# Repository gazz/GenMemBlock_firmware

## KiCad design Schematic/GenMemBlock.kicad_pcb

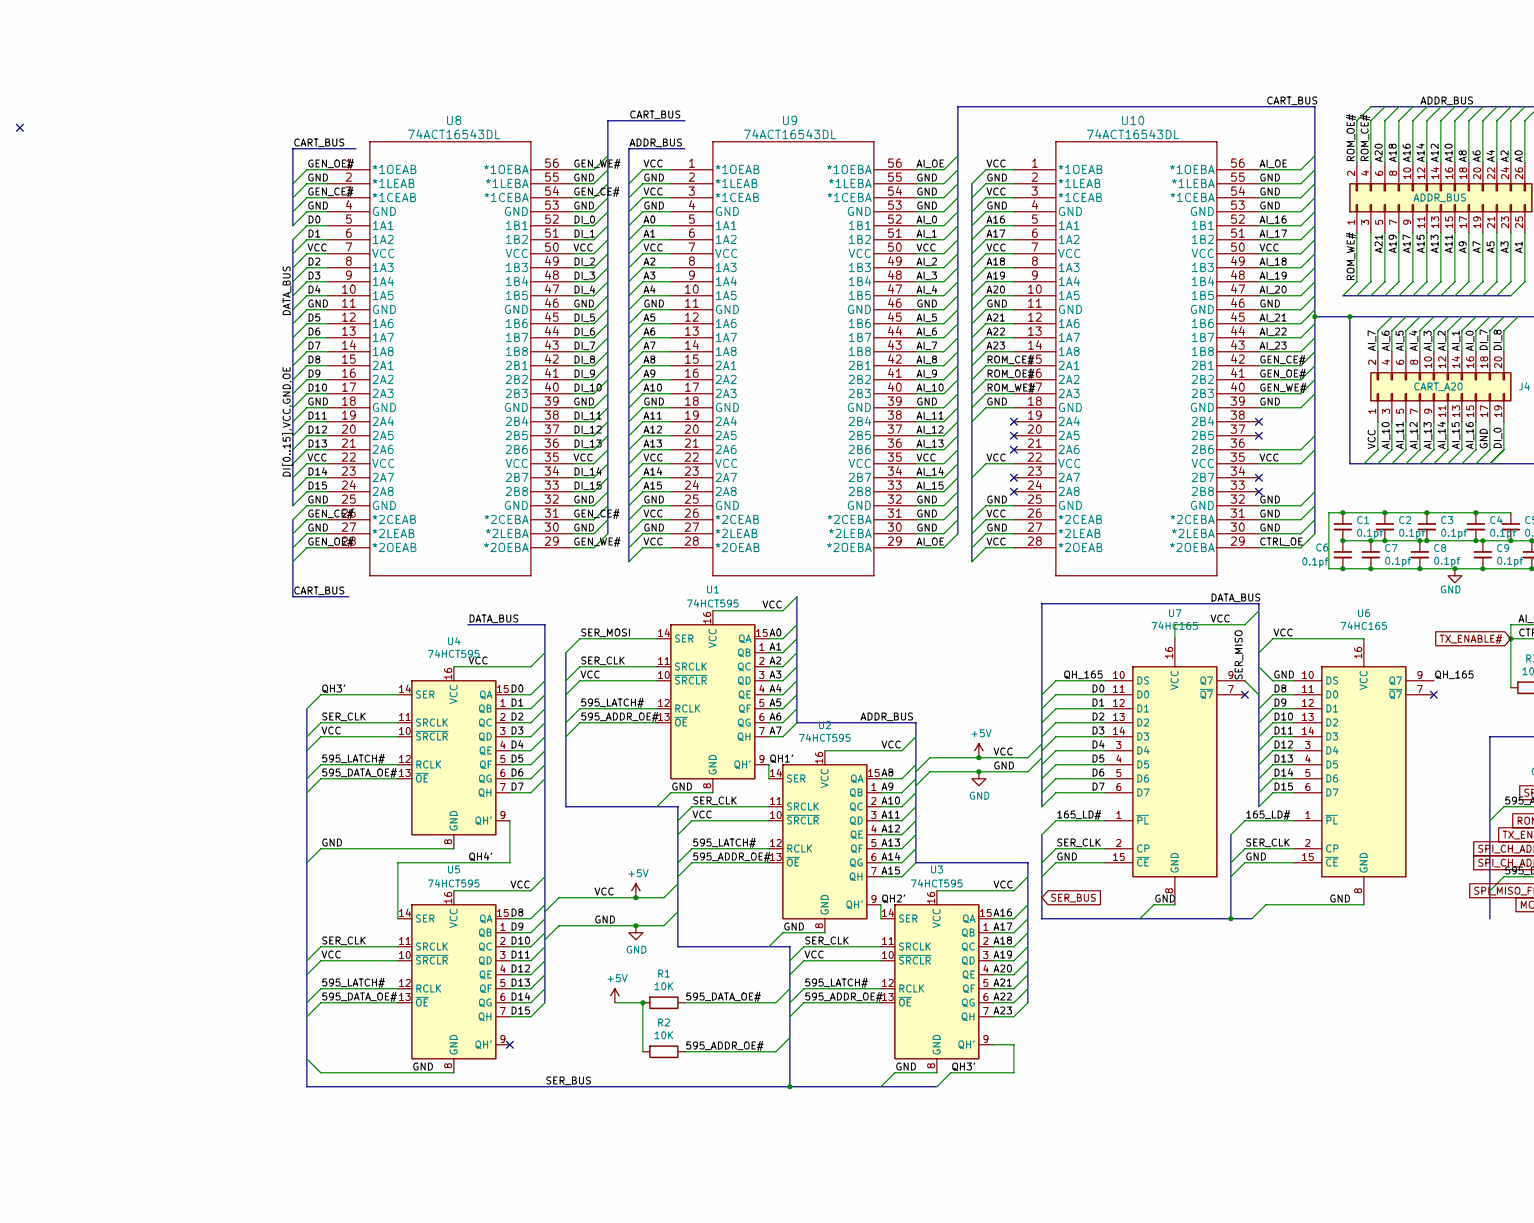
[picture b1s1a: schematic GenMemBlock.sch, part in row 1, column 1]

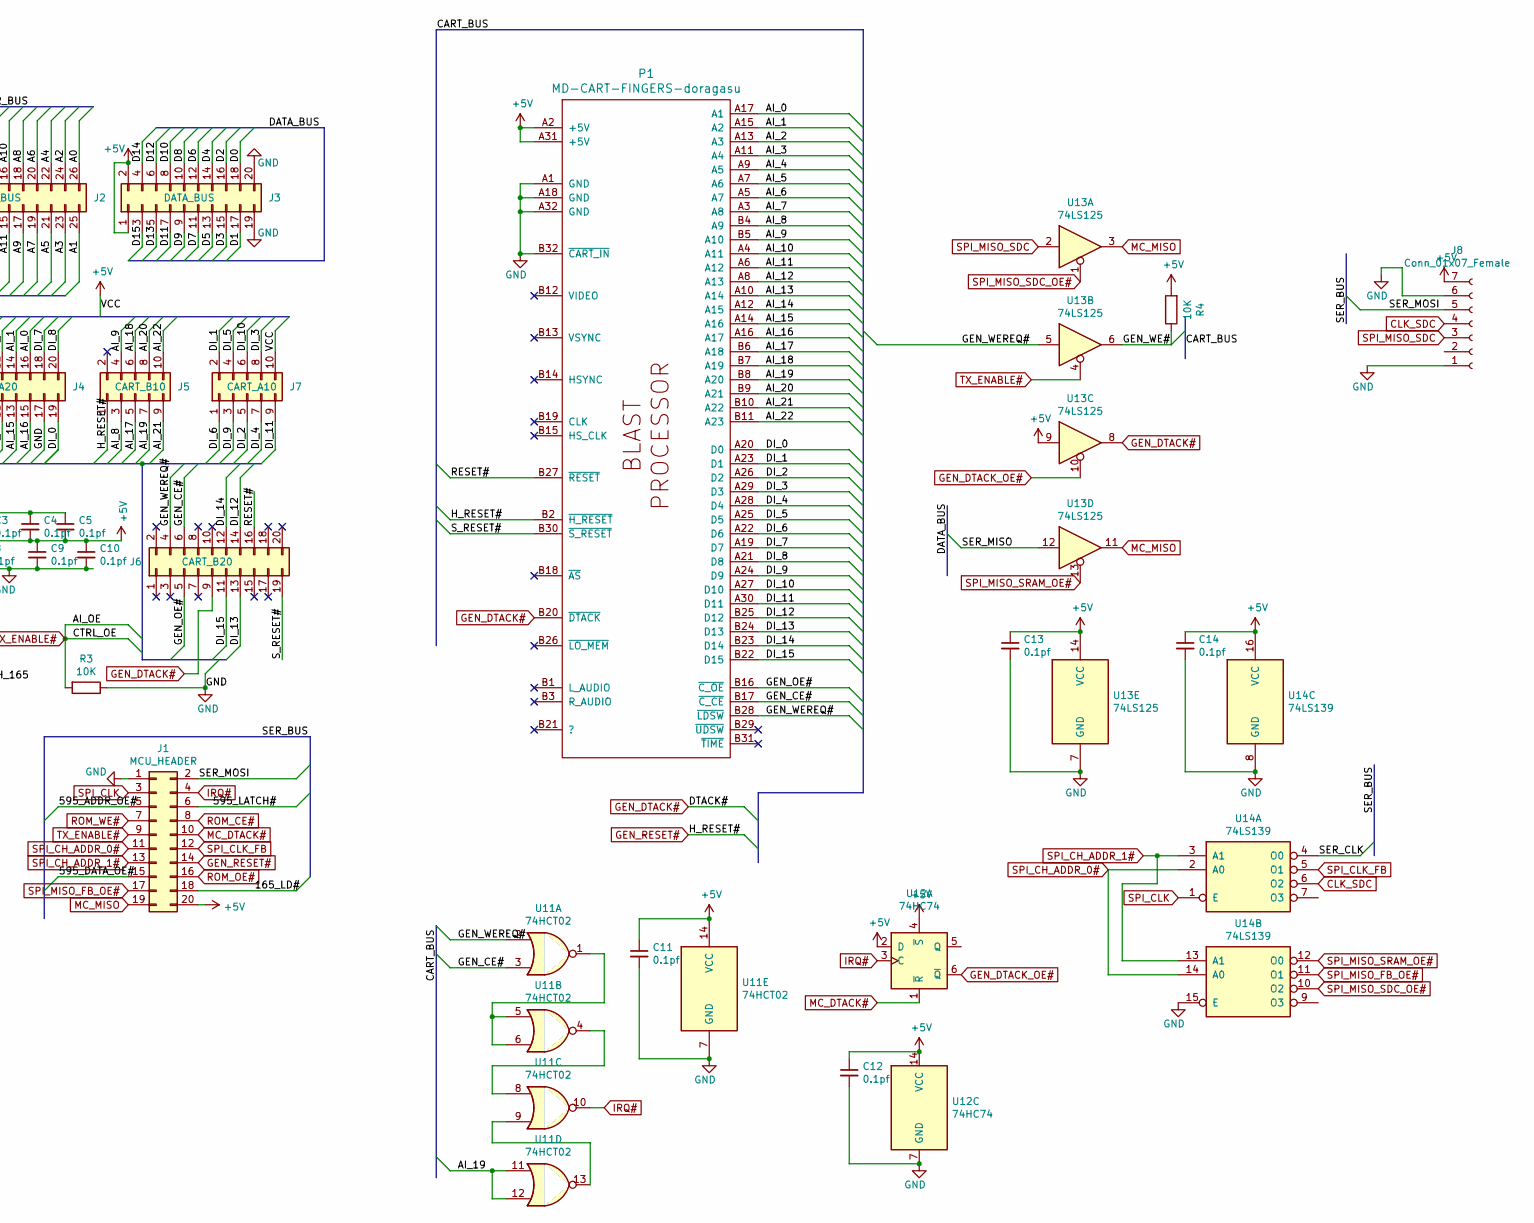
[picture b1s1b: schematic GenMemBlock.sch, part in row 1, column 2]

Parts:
C1, C2, C3, C4, C5, C6, C7, C8, C9, C10, C11, C12, C13, C14: 0.1pf; C_0805_2012Metric_Pad1.18x1.45mm_HandSolder
J1: MCU_HEADER; PinHeader_2x10_P2.54mm_Vertical
J2: ADDR_BUS; PinHeader_2x13_P2.54mm_Vertical
J3: DATA_BUS; PinHeader_2x10_P2.54mm_Vertical
J4: CART_A20; PinHeader_2x10_P2.54mm_Vertical
J5: CART_B10; PinHeader_2x05_P2.54mm_Vertical
J6: CART_B20; PinHeader_2x10_P2.54mm_Vertical
J7: CART_A10; PinHeader_2x05_P2.54mm_Vertical
J8: Conn_01x07_Female; PinHeader_1x07_P2.54mm_Vertical
P1: MD-CART-FINGERS-doragasu; md-cart
R1, R2, R3, R4: 10K; R_0805_2012Metric_Pad1.20x1.40mm_HandSolder
U1, U2, U3, U4, U5: 74HCT595; SOIC-16_3.9x9.9mm_P1.27mm
U6, U7: 74HC165; SSOP-16_5.3x6.2mm_P0.65mm
U8, U9, U10: 74ACT16543DL
U11: 74HCT02; TSSOP-14_4.4x5mm_P0.65mm
U12: 74HC74; TSSOP-14_4.4x5mm_P0.65mm
U13: 74LS125; TSSOP-14_4.4x5mm_P0.65mm
U14: 74LS139; TSSOP-16_4.4x5mm_P0.65mm

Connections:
+5V: C1.2, C2.2, C3.2, C4.2, C5.2, C6.1, C7.1, C8.1, C9.1, C10.1, C11.1, C12.1, C13.1, C14.1, J1.20, J3.1, J3.2, J4.1, J7.10, J8.7, P1.A2 (+5V), P1.A31 (+5V), R1.2, R2.2, R4.2, U1.10 (~SRCLR), U1.16 (VCC), U2.10 (~SRCLR), U2.16 (VCC), U3.10 (~SRCLR), U3.16 (VCC), U4.10 (~SRCLR), U4.16 (VCC), U5.10 (~SRCLR), U5.16 (VCC), U6.16 (VCC), U7.16 (VCC), U8.7 (VCC), U8.22 (VCC), U8.35 (VCC), U8.50 (VCC), U9.1 (*1OEAB), U9.3 (*1CEAB), U9.7 (VCC), U9.22 (VCC), U9.26 (*2CEAB), U9.28 (*2OEAB), U9.35 (VCC), U9.50 (VCC), U10.1 (*1OEAB), U10.3 (*1CEAB), U10.7 (VCC), U10.22 (VCC), U10.26 (*2CEAB), U10.28 (*2OEAB), U10.35 (VCC), U10.50 (VCC), U11.14 (VCC), U12.2 (D), U12.4 (~S), U12.14 (VCC), U13.9, U13.14 (VCC), U14.16 (VCC)
/165_LD#: J1.18, U6.1 (~PL), U7.1 (~PL)
/595_ADDR_OE#: J1.5, R2.1, U1.13 (~OE), U2.13 (~OE), U3.13 (~OE)
/595_DATA_OE#: J1.15, R1.1, U4.13 (~OE), U5.13 (~OE)
/595_LATCH#: J1.6, U1.12 (RCLK), U2.12 (RCLK), U3.12 (RCLK), U4.12 (RCLK), U5.12 (RCLK)
/A0: J2.26, U1.15 (QA), U9.5 (1A1)
/A1: J2.25, U1.1 (QB), U9.6 (1A2)
/A2: J2.24, U1.2 (QC), U9.8 (1A3)
/A3: J2.23, U1.3 (QD), U9.9 (1A4)
/A4: J2.22, U1.4 (QE), U9.10 (1A5)
/A5: J2.21, U1.5 (QF), U9.12 (1A6)
/A6: J2.20, U1.6 (QG), U9.13 (1A7)
/A7: J2.19, U1.7 (QH), U9.14 (1A8)
/A8: J2.18, U2.15 (QA), U9.15 (2A1)
/A9: J2.17, U2.1 (QB), U9.16 (2A2)
/A10: J2.16, U2.2 (QC), U9.17 (2A3)
/A11: J2.15, U2.3 (QD), U9.19 (2A4)
/A12: J2.14, U2.4 (QE), U9.20 (2A5)
/A13: J2.13, U2.5 (QF), U9.21 (2A6)
/A14: J2.12, U2.6 (QG), U9.23 (2A7)
/A15: J2.11, U2.7 (QH), U9.24 (2A8)
/A16: J2.10, U3.15 (QA), U10.5 (1A1)
/A17: J2.9, U3.1 (QB), U10.6 (1A2)
/A18: J2.8, U3.2 (QC), U10.8 (1A3)
/A19: J2.7, U3.3 (QD), U10.9 (1A4)
/A20: J2.6, U3.4 (QE), U10.10 (1A5)
/A21: J2.5, U3.5 (QF), U10.12 (1A6)
/A22: U3.6 (QG), U10.13 (1A7)
/A23: U3.7 (QH), U10.14 (1A8)
/AI_0: J4.16, P1.A17 (A1), U9.52 (1B1)
/AI_1: J4.14, P1.A15 (A2), U9.51 (1B2)
/AI_2: J4.12, P1.A13 (A3), U9.49 (1B3)
/AI_3: J4.10, P1.A11 (A4), U9.48 (1B4)
/AI_4: J4.8, P1.A9 (A5), U9.47 (1B5)
/AI_5: J4.6, P1.A7 (A6), U9.45 (1B6)
/AI_6: J4.4, P1.A5 (A7), U9.44 (1B7)
/AI_7: J4.2, P1.A3 (A8), U9.43 (1B8)
/AI_8: J5.3, P1.B4 (A9), U9.42 (2B1)
/AI_9: J5.4, P1.B5 (A10), U9.41 (2B2)
/AI_10: J4.3, P1.A4 (A11), U9.40 (2B3)
/AI_11: J4.5, P1.A6 (A12), U9.38 (2B4)
/AI_12: J4.7, P1.A8 (A13), U9.37 (2B5)
/AI_13: J4.9, P1.A10 (A14), U9.36 (2B6)
/AI_14: J4.11, P1.A12 (A15), U9.34 (2B7)
/AI_15: J4.13, P1.A14 (A16), U9.33 (2B8)
/AI_16: J4.15, P1.A16 (A17), U10.52 (1B1)
/AI_17: J5.5, P1.B6 (A18), U10.51 (1B2)
/AI_18: J5.6, P1.B7 (A19), U10.49 (1B3)
/AI_19: J5.7, P1.B8 (A20), U10.48 (1B4), U11.11, U11.12
/AI_20: J5.8, P1.B9 (A21), U10.47 (1B5)
/AI_21: J5.9, P1.B10 (A22), U10.45 (1B6)
/AI_22: J5.10, P1.B11 (A23), U10.44 (1B7)
/AI_23: U10.43 (1B8)
/D0: J3.18, U4.15 (QA), U7.11 (D0), U8.5 (1A1)
/D1: J3.17, U4.1 (QB), U7.12 (D1), U8.6 (1A2)
/D2: J3.16, U4.2 (QC), U7.13 (D2), U8.8 (1A3)
/D3: J3.15, U4.3 (QD), U7.14 (D3), U8.9 (1A4)
/D4: J3.14, U4.4 (QE), U7.3 (D4), U8.10 (1A5)
/D5: J3.13, U4.5 (QF), U7.4 (D5), U8.12 (1A6)
/D6: J3.12, U4.6 (QG), U7.5 (D6), U8.13 (1A7)
/D7: J3.11, U4.7 (QH), U7.6 (D7), U8.14 (1A8)
/D8: J3.10, U5.15 (QA), U6.11 (D0), U8.15 (2A1)
/D9: J3.9, U5.1 (QB), U6.12 (D1), U8.16 (2A2)
/D10: J3.8, U5.2 (QC), U6.13 (D2), U8.17 (2A3)
/D11: J3.7, U5.3 (QD), U6.14 (D3), U8.19 (2A4)
/D12: J3.6, U5.4 (QE), U6.3 (D4), U8.20 (2A5)
/D13: J3.5, U5.5 (QF), U6.4 (D5), U8.21 (2A6)
/D14: J3.4, U5.6 (QG), U6.5 (D6), U8.23 (2A7)
/D15: J3.3, U5.7 (QH), U6.6 (D7), U8.24 (2A8)
/DI_0: J4.19, P1.A20 (D0), U8.52 (1B1)
/DI_1: J7.2, P1.A23 (D1), U8.51 (1B2)
/DI_2: J7.5, P1.A26 (D2), U8.49 (1B3)
/DI_3: J7.8, P1.A29 (D3), U8.48 (1B4)
/DI_4: J7.7, P1.A28 (D4), U8.47 (1B5)
/DI_5: J7.4, P1.A25 (D5), U8.45 (1B6)
/DI_6: J7.1, P1.A22 (D6), U8.44 (1B7)
/DI_7: J4.18, P1.A19 (D7), U8.43 (1B8)
/DI_8: J4.20, P1.A21 (D8), U8.42 (2B1)
/DI_9: J7.3, P1.A24 (D9), U8.41 (2B2)
/DI_10: J7.6, P1.A27 (D10), U8.40 (2B3)
/DI_11: J7.9, P1.A30 (D11), U8.38 (2B4)
/DI_12: J6.14, P1.B25 (D12), U8.37 (2B5)
/DI_13: J6.13, P1.B24 (D13), U8.36 (2B6)
/DI_14: J6.12, P1.B23 (D14), U8.34 (2B7)
/DI_15: J6.11, P1.B22 (D15), U8.33 (2B8)
/GEN_CE#: J6.6, P1.B17 (~C_CE), U8.3 (*1CEAB), U8.26 (*2CEAB), U8.31 (*2CEBA), U8.54 (*1CEBA), U10.42 (2B1), U11.3
/GEN_OE#: J6.5, P1.B16 (~C_OE), U8.1 (*1OEAB), U8.28 (*2OEAB), U10.41 (2B2)
/GEN_WE#: R4.1, U8.29 (*2OEBA), U8.56 (*1OEBA), U10.40 (2B3), U13.6
/GEN_WEREQ#: J6.4, P1.B28 (~LDSW), U11.2, U13.5
/QH1': U1.9 (QH'), U2.14 (SER)
/QH2': U2.9 (QH'), U3.14 (SER)
/QH3': U3.9 (QH'), U4.14 (SER)
/QH4': U4.9 (QH'), U5.14 (SER)
/QH_165: U6.9 (Q7), U7.10 (DS)
/RESET#: J6.16, P1.B27 (~RESET)
/SER_CLK: U1.11 (SRCLK), U2.11 (SRCLK), U3.11 (SRCLK), U4.11 (SRCLK), U5.11 (SRCLK), U6.2 (CP), U7.2 (CP), U14.4 (O0)
/SER_MISO: U7.9 (Q7), U13.12
/SER_MOSI: J1.2, J8.5, U1.14 (SER)
/S_RESET#: J6.19, P1.B30 (~S_RESET)
CLK_SDC: J8.4, U14.6 (O2)
GEN_DTACK#: J6.9, P1.B20 (~DTACK), U13.8
GEN_DTACK_OE#: U12.6 (~Q), U13.10
GEN_RESET#: J1.14, J5.1, P1.B2 (~H_RESET)
GND: C1.1, C2.1, C3.1, C4.1, C5.1, C6.2, C7.2, C8.2, C9.2, C10.2, C11.2, C12.2, C13.2, C14.2, J1.1, J3.19, J3.20, J4.17, J8.1, J8.6, P1.A1 (GND), P1.A18 (GND), P1.A32 (GND), P1.B32 (~CART_IN), R3.1, U1.8 (GND), U2.8 (GND), U3.8 (GND), U4.8 (GND), U5.8 (GND), U6.8 (GND), U6.10 (DS), U6.15 (~CE), U7.8 (GND), U7.15 (~CE), U8.2 (*1LEAB), U8.4 (GND), U8.11 (GND), U8.18 (GND), U8.25 (GND), U8.27 (*2LEAB), U8.30 (*2LEBA), U8.32 (GND), U8.39 (GND), U8.46 (GND), U8.53 (GND), U8.55 (*1LEBA), U9.2 (*1LEAB), U9.4 (GND), U9.11 (GND), U9.18 (GND), U9.25 (GND), U9.27 (*2LEAB), U9.30 (*2LEBA), U9.31 (*2CEBA), U9.32 (GND), U9.39 (GND), U9.46 (GND), U9.53 (GND), U9.54 (*1CEBA), U9.55 (*1LEBA), U10.2 (*1LEAB), U10.4 (GND), U10.11 (GND), U10.18 (GND), U10.25 (GND), U10.27 (*2LEAB), U10.30 (*2LEBA), U10.31 (*2CEBA), U10.32 (GND), U10.39 (GND), U10.46 (GND), U10.53 (GND), U10.54 (*1CEBA), U10.55 (*1LEBA), U11.7 (GND), U12.7 (GND), U13.7 (GND), U14.8 (GND), U14.15 (E)
IRQ#: J1.4, U11.10, U12.3 (C)
MC_DTACK#: J1.10, U12.1 (~R)
MC_MISO: J1.19, U13.3, U13.11
unnamed: U11.1, U11.5, U11.6
unnamed: U11.4, U11.8
unnamed: U11.9, U11.13
ROM_CE#: J1.8, J2.4, U10.15 (2A1)
ROM_OE#: J1.16, J2.2, U10.16 (2A2)
ROM_WE#: J1.7, J2.1, U10.17 (2A3)
SPI_CH_ADDR_0#: J1.11, U14.2 (A0), U14.14 (A0)
SPI_CH_ADDR_1#: J1.13, U14.3 (A1), U14.13 (A1)
SPI_CLK: J1.3, U14.1 (E)
SPI_CLK_FB: J1.12, U14.5 (O1)
SPI_MISO_FB_OE#: J1.17, U14.11 (O1)
SPI_MISO_SDC: J8.3, U13.2
SPI_MISO_SDC_OE#: U13.1, U14.10 (O2)
SPI_MISO_SRAM_OE#: U13.13, U14.12 (O0)
TX_ENABLE#: J1.9, R3.2, U9.29 (*2OEBA), U9.56 (*1OEBA), U10.29 (*2OEBA), U10.56 (*1OEBA), U13.4

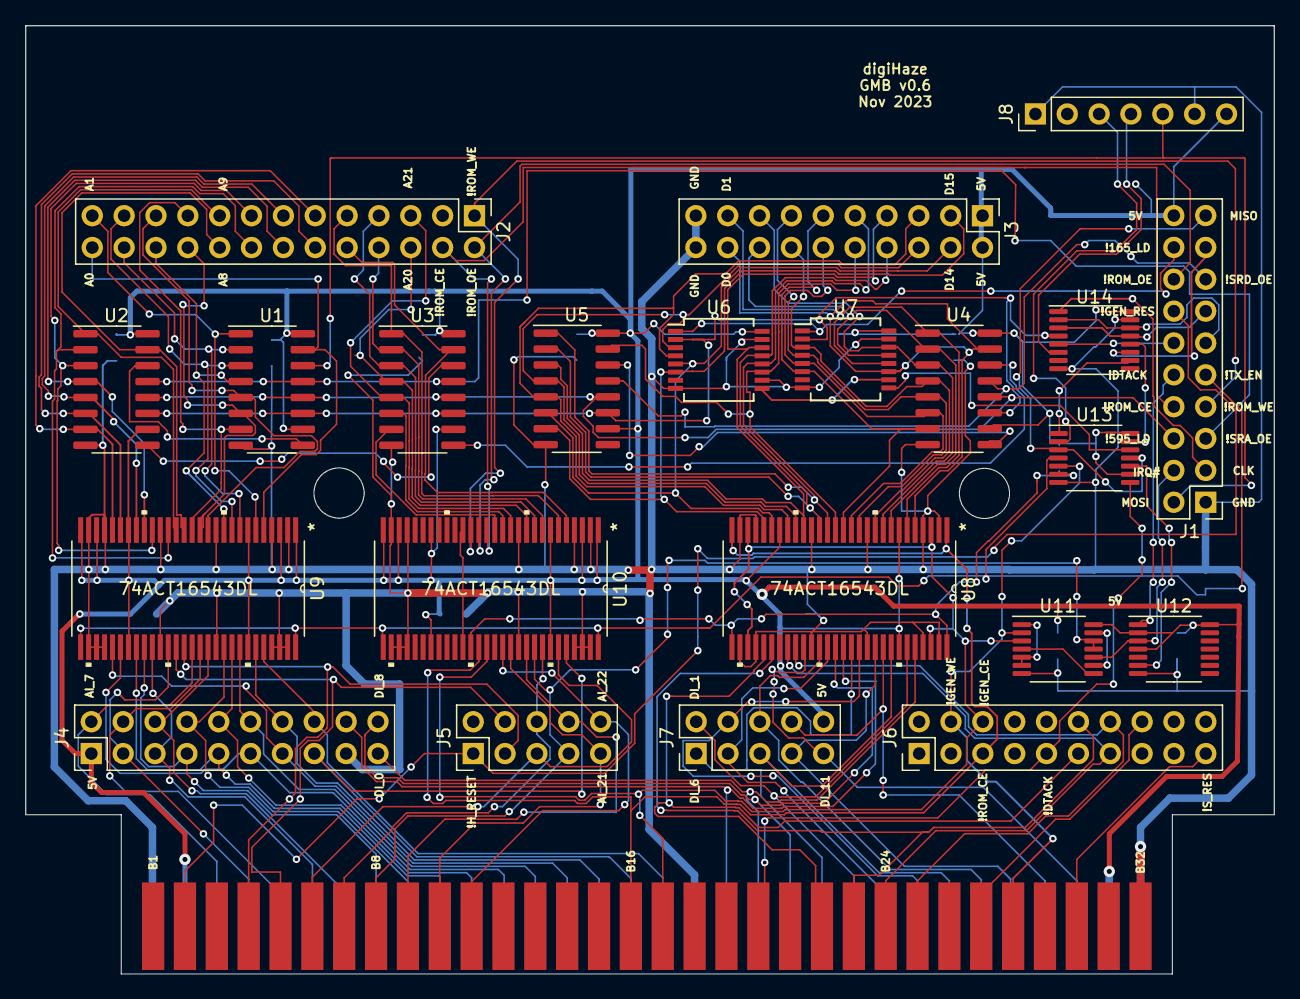
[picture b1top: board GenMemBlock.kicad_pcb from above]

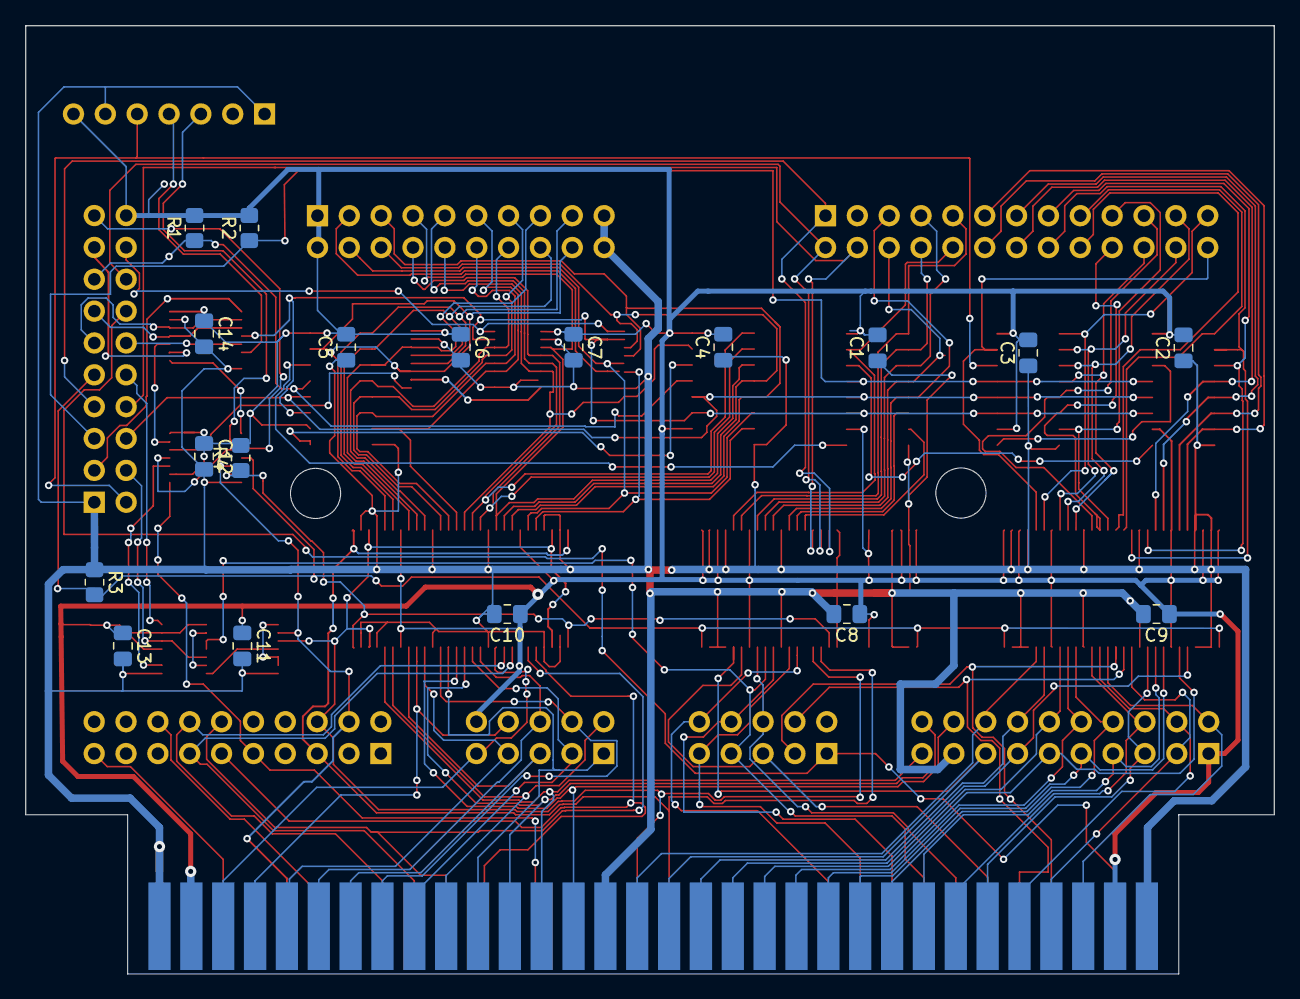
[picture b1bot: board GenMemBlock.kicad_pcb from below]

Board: 4 copper layers, 99.6 x 75.6 mm, 41 parts (18 on the bottom side), 121 nets.

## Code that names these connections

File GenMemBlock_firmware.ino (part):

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
// line buffer control
#define SR595_LD 6
#define PIN_ROM_WE 8
#define PIN_ROM_CE A3
#define PIN_ROM_OE A2

#define SD_CS_PIN A0

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    controlOut(F_SL165_LD, false, true);
    digitalWrite(SR595_LD, LOW);
    
    digitalWrite(PIN_ROM_WE, HIGH);

    pinMode(PIN_ROM_WE, OUTPUT);
    pinMode(PIN_ROM_OE, OUTPUT);
    pinMode(PIN_ROM_CE, OUTPUT);
    
    controlOut(F_GEN_TX_EN, true, true);

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//  digitalWrite(SR595_LD, LOW);
//  controlOut(0xff, true, true);
  digitalWrite(SR595_LD, LOW);
  // digitalWrite(PIN_ROM_WE, HIGH);
  // go high impedience on WE pin
  pinMode(PIN_ROM_WE, INPUT);
  pinMode(PIN_ROM_OE, INPUT);
  pinMode(PIN_ROM_CE, INPUT);

  controlOut(0xff, true, true);
  controlOut(F_GEN_TX_EN, false, true);
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  digitalWrite(SR595_LD, LOW);
  pinMode(SR595_LD, OUTPUT);

  digitalWrite(PIN_ROM_WE, HIGH);
  pinMode(PIN_ROM_WE, OUTPUT);

  controlOut(0xff, true, true);
  
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  }
#endif
 
  digitalWrite(PIN_ROM_OE, HIGH);
  digitalWrite(PIN_ROM_CE, LOW);
  controlOut(F_SRA_OE | F_SRD_OE, false, true);

  for (unsigned long i = 0; i < bufferSize; i++) {
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    shiftOutAddressAndData(target_address, flipBytes ? flipIntBytes(buffer[i]) : buffer[i]);

    // we have PORTB pins are offset by 8
    // PORTB &= ~(1 << (8 - PIN_ROM_WE));
    // PORTB |= 1 << (8 - PIN_ROM_WE);
    digitalWrite(PIN_ROM_WE, LOW);
    digitalWrite(PIN_ROM_WE, HIGH);

    if (true) {
      continue;
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  
  outAddress(addr24bit);

  digitalWrite(PIN_ROM_OE, LOW);
  digitalWrite(PIN_ROM_CE, LOW);

  controlOut(F_SL165_LD, false, true);
  controlOut(F_SL165_LD, true, true);
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
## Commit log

2021-09-03 Basic firmware with a few actions via serial interface
2021-09-14 latest firmware with full read/write/verify functionality
2021-10-10 added faster write + moved string constants to progmem to have a bigger playground available
2021-10-16 fixed paged write to calculate the address correctly, control passover fixes
2021-10-16 reenabled rom size validation
2021-11-23 read via cart slot add-on
2021-12-30 trace logging + small bugfixes around writing data/locking data
2021-12-30 added schematic
2022-01-23 working version v3
2022-09-04 moved to SPI bus instead of direct control, adds SD Card
2022-10-08 byte upload, metrics, optimizations
2023-08-24 interrupt handler from genesys
2023-08-24 propagate WE# from cart side
2023-09-01 read/write gencart, removed reset header and use H_RESET#
2023-10-29 sega/microcontroller interop
2023-11-10 ROM_CE & ROM_OE on dedicated lines to allow for high-z mode
2023-11-16 isolated common logic chips from mc board
2023-11-16 sdcard pinout
2023-11-16 sdcard wiring
2023-11-24 moved to single board with SPI splitter

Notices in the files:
parts and their libraries:
Copyright 2021 Accelerated Designs. All rights reserved.
